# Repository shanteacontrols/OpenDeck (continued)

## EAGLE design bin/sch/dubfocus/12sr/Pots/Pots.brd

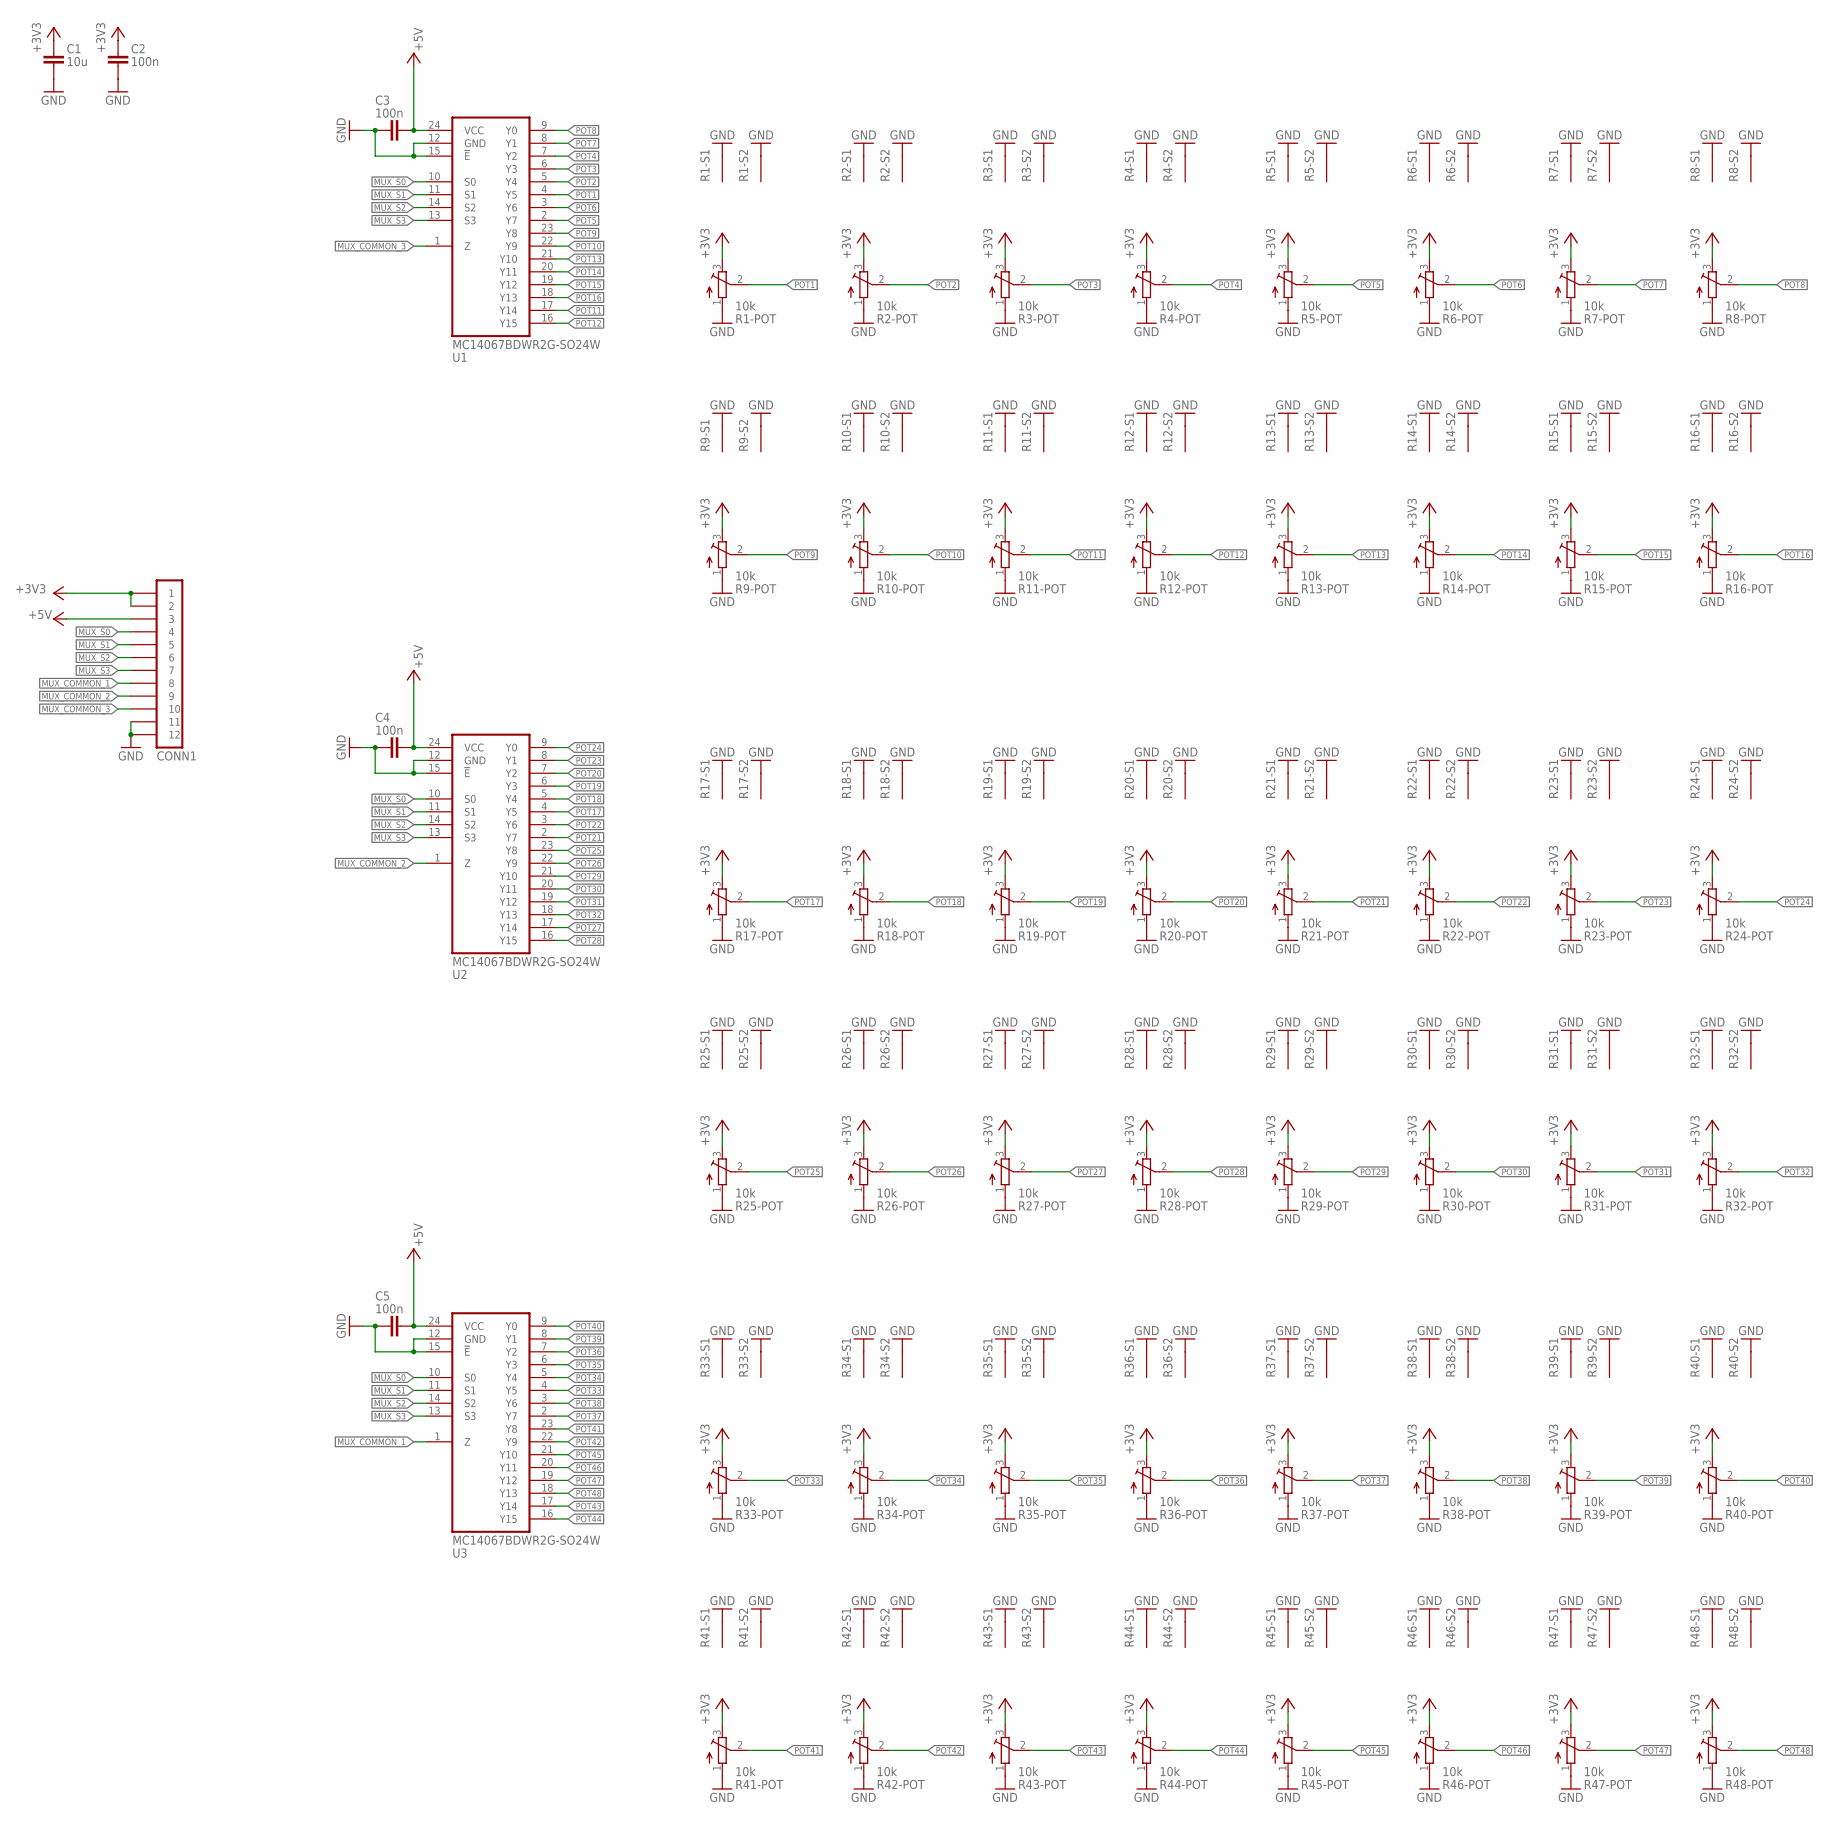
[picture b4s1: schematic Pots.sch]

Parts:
C1: 10u; C0805
C2, C3, C4, C5: 100n; C0805
CONN1: PINHD-1X12-SMD; MOLEX-52271-1279
R1, R2, R3, R4, R5, R6, R7, R8, R9, R10, R11, R12, R13, R14, R15, R16, R17, R18, R19, R20, R21, R22, R23, R24, R25, R26, R27, R28, R29, R30, R31, R32, R33, R34, R35, R36, R37, R38, R39, R40, R41, R42, R43, R44, R45, R46, R47, R48: 10k; PTV09A-4025F-B103
U1, U2, U3: MC14067BDWR2G-SO24W; SO24-W

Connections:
+3V3: C1.1, C2.1, CONN1.1, CONN1.2, R1.3, R2.3, R3.3, R4.3, R5.3, R6.3, R7.3, R8.3, R9.3, R10.3, R11.3, R12.3, R13.3, R14.3, R15.3, R16.3, R17.3, R18.3, R19.3, R20.3, R21.3, R22.3, R23.3, R24.3, R25.3, R26.3, R27.3, R28.3, R29.3, R30.3, R31.3, R32.3, R33.3, R34.3, R35.3, R36.3, R37.3, R38.3, R39.3, R40.3, R41.3, R42.3, R43.3, R44.3, R45.3, R46.3, R47.3, R48.3
+5V: C3.2, C4.2, C5.2, CONN1.3, U1.24 (VCC), U2.24 (VCC), U3.24 (VCC)
GND: C1.2, C2.2, C3.1, C4.1, C5.1, CONN1.11, CONN1.12, R1.1, R1.S1 (S), R1.S2 (S), R2.1, R2.S1 (S), R2.S2 (S), R3.1, R3.S1 (S), R3.S2 (S), R4.1, R4.S1 (S), R4.S2 (S), R5.1, R5.S1 (S), R5.S2 (S), R6.1, R6.S1 (S), R6.S2 (S), R7.1, R7.S1 (S), R7.S2 (S), R8.1, R8.S1 (S), R8.S2 (S), R9.1, R9.S1 (S), R9.S2 (S), R10.1, R10.S1 (S), R10.S2 (S), R11.1, R11.S1 (S), R11.S2 (S), R12.1, R12.S1 (S), R12.S2 (S), R13.1, R13.S1 (S), R13.S2 (S), R14.1, R14.S1 (S), R14.S2 (S), R15.1, R15.S1 (S), R15.S2 (S), R16.1, R16.S1 (S), R16.S2 (S), R17.1, R17.S1 (S), R17.S2 (S), R18.1, R18.S1 (S), R18.S2 (S), R19.1, R19.S1 (S), R19.S2 (S), R20.1, R20.S1 (S), R20.S2 (S), R21.1, R21.S1 (S), R21.S2 (S), R22.1, R22.S1 (S), R22.S2 (S), R23.1, R23.S1 (S), R23.S2 (S), R24.1, R24.S1 (S), R24.S2 (S), R25.1, R25.S1 (S), R25.S2 (S), R26.1, R26.S1 (S), R26.S2 (S), R27.1, R27.S1 (S), R27.S2 (S), R28.1, R28.S1 (S), R28.S2 (S), R29.1, R29.S1 (S), R29.S2 (S), R30.1, R30.S1 (S), R30.S2 (S), R31.1, R31.S1 (S), R31.S2 (S), R32.1, R32.S1 (S), R32.S2 (S), R33.1, R33.S1 (S), R33.S2 (S), R34.1, R34.S1 (S), R34.S2 (S), R35.1, R35.S1 (S), R35.S2 (S), R36.1, R36.S1 (S), R36.S2 (S), R37.1, R37.S1 (S), R37.S2 (S), R38.1, R38.S1 (S), R38.S2 (S), R39.1, R39.S1 (S), R39.S2 (S), R40.1, R40.S1 (S), R40.S2 (S), R41.1, R41.S1 (S), R41.S2 (S), R42.1, R42.S1 (S), R42.S2 (S), R43.1, R43.S1 (S), R43.S2 (S), R44.1, R44.S1 (S), R44.S2 (S), R45.1, R45.S1 (S), R45.S2 (S), R46.1, R46.S1 (S), R46.S2 (S), R47.1, R47.S1 (S), R47.S2 (S), R48.1, R48.S1 (S), R48.S2 (S), U1.12 (GND), U1.15 (!E), U2.12 (GND), U2.15 (!E), U3.12 (GND), U3.15 (!E)
MUX_COMMON_1: CONN1.8, U3.1 (Z)
MUX_COMMON_2: CONN1.9, U2.1 (Z)
MUX_COMMON_3: CONN1.10, U1.1 (Z)
MUX_S0: CONN1.4, U1.10 (S0), U2.10 (S0), U3.10 (S0)
MUX_S1: CONN1.5, U1.11 (S1), U2.11 (S1), U3.11 (S1)
MUX_S2: CONN1.6, U1.14 (S2), U2.14 (S2), U3.14 (S2)
MUX_S3: CONN1.7, U1.13 (S3), U2.13 (S3), U3.13 (S3)
POT1: R1.2, U1.4 (Y5)
POT2: R2.2, U1.5 (Y4)
POT3: R3.2, U1.6 (Y3)
POT4: R4.2, U1.7 (Y2)
POT5: R5.2, U1.2 (Y7)
POT6: R6.2, U1.3 (Y6)
POT7: R7.2, U1.8 (Y1)
POT8: R8.2, U1.9 (Y0)
POT9: R9.2, U1.23 (Y8)
POT10: R10.2, U1.22 (Y9)
POT11: R11.2, U1.17 (Y14)
POT12: R12.2, U1.16 (Y15)
POT13: R13.2, U1.21 (Y10)
POT14: R14.2, U1.20 (Y11)
POT15: R15.2, U1.19 (Y12)
POT16: R16.2, U1.18 (Y13)
POT17: R17.2, U2.4 (Y5)
POT18: R18.2, U2.5 (Y4)
POT19: R19.2, U2.6 (Y3)
POT20: R20.2, U2.7 (Y2)
POT21: R21.2, U2.2 (Y7)
POT22: R22.2, U2.3 (Y6)
POT23: R23.2, U2.8 (Y1)
POT24: R24.2, U2.9 (Y0)
POT25: R25.2, U2.23 (Y8)
POT26: R26.2, U2.22 (Y9)
POT27: R27.2, U2.17 (Y14)
POT28: R28.2, U2.16 (Y15)
POT29: R29.2, U2.21 (Y10)
POT30: R30.2, U2.20 (Y11)
POT31: R31.2, U2.19 (Y12)
POT32: R32.2, U2.18 (Y13)
POT33: R33.2, U3.4 (Y5)
POT34: R34.2, U3.5 (Y4)
POT35: R35.2, U3.6 (Y3)
POT36: R36.2, U3.7 (Y2)
POT37: R37.2, U3.2 (Y7)
POT38: R38.2, U3.3 (Y6)
POT39: R39.2, U3.8 (Y1)
POT40: R40.2, U3.9 (Y0)
POT41: R41.2, U3.23 (Y8)
POT42: R42.2, U3.22 (Y9)
POT43: R43.2, U3.17 (Y14)
POT44: R44.2, U3.16 (Y15)
POT45: R45.2, U3.21 (Y10)
POT46: R46.2, U3.20 (Y11)
POT47: R47.2, U3.19 (Y12)
POT48: R48.2, U3.18 (Y13)

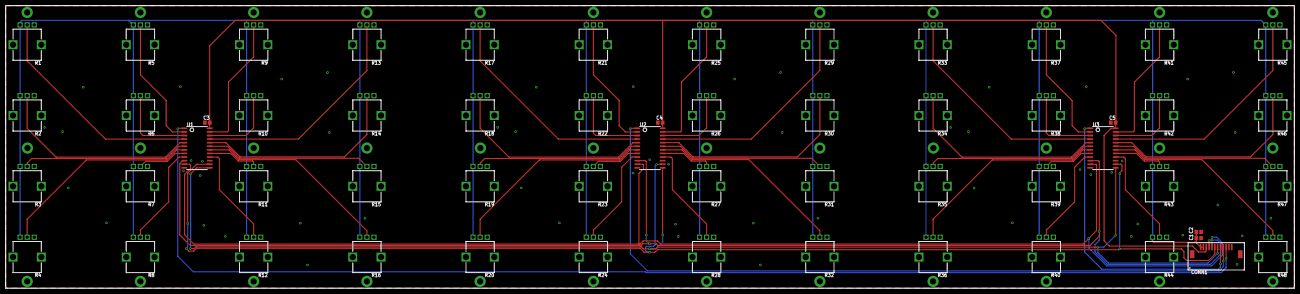
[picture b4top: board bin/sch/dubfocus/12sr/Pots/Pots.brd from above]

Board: 2 copper layers, 455.2 x 99.8 mm, 57 parts (0 on the bottom side), 58 nets.

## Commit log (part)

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2023-05-30 tests/bootloader: don't use internal board api
2023-05-31 clang_tidy_wrapper.sh: use consistent spacing
2023-05-31 vscode: don't hide build dir and compile_commands
2023-05-31 dockerfile: use clang from ubuntu repos
2023-06-01 scripts/dev.sh: always pull the latest image
2023-06-01 dockerfile: fixup comments
2023-06-01 misc: linting
2023-06-04 rewrite the build system in cmake
2023-06-04 tests: guard flash functions with ifdef
2023-06-04 vscode: update devcontainer.json
2023-06-04 update core module
2023-06-04 build/board: rework internal include directories
2023-06-04 board: remove unused function
2023-06-04 tests/hw: make the usage of hw controller configurable in yml config
2023-06-10 build/tests: fix incorrect paths in execute_process
2023-06-10 vscode: fix incorrect path for workspaceFolder
2023-06-10 update sysexconf module
2023-06-10 update midi module
2023-06-10 build/tests: remove redundant include
2023-06-10 build: don't include the entire modules subdir
2023-06-11 build: don't include internal board header in generated target header
2023-06-26 build: move code formatting to script for simpler usage
    otherwise bunch of character escapes are needed in cmake to make it work
2023-06-29 build: fix broken 4051 mux pin generator
2023-06-29 leds: fix invalid retrieval of blink speed
2023-06-29 tests/leds: add tests for single value control types
2023-06-29 system: allow setting 0 as led activation value
2023-09-01 build/scripts: fix muxonmux driver symbol not being generated
2023-10-12 bootloader: remove unsupported code paths
2023-10-14 build: build generated app sources for flashgen target
2023-10-14 touchscreen: don't generate icons from images (unused)
2023-10-15 remove support for viewtech touchscreens
2023-10-16 tests/leds: fix warnings
2023-10-16 build: use named arguments for gen_mcu.sh script
2023-10-26 system: add support for sending din midi clock
2023-10-26 build/gen_mcu.sh: generate only if dir doesn't exist
2023-10-28 sch: place dubfocus 16c schematics in dedicated dir
2024-02-18 build/scripts: allow arbitrary number of daisy chained max7219
2024-02-20 build: always build tests (external project)
2024-02-21 encoders: enable setting lower and upper limit for certain message types
2024-02-21 database: remove unused code
2024-02-21 database: move internal block read/write to dedicated functions
2024-02-21 system: allow disabling of forced refresh after preset change
2024-02-21 display: restore old viewtech display support
2024-03-06 ci: switch to github registry
2024-03-06 scripts/flashing/bmp: use gdb instead of arm-none-eabi-gdb
2024-03-06 ci: update actions
2024-03-06 docker-compose: consistency tweaks
2024-03-06 dockerfile: install nrf command line tools
2024-03-06 build: rework linting script
2024-03-06 vscode: install cortex debug extension
2024-03-06 app: fix include path for logger
2024-03-06 ci: save/restore cache
2024-03-13 display: shorten the MMC record string to fit on display
2024-03-13 display: rework strings and in/out text on display
2024-03-13 display: use U8X8_WITH_USER_PTR symbol for u8x8 lib
2024-03-13 display: show preset number
2024-03-13 display: remove unused variable
2024-03-14 flashgen: namespace the generated mcu header to avoid issues
2024-03-15 system: make preset change with program change in optional
2024-04-02 scripts/flashing: fix pyocd script
2024-04-03 build: regenerate and merge the flash config when application changes
2024-04-06 build: use BUILD_ALWAYS in a consistent way for external projects
    This will ensure that flashgen/sysexgen are rebuilt if they change
2024-04-06 scripts: use sudo in flashing scripts
    This avoids the need for the users to setup udev rules before flashing is possible
2024-04-08 leds: implement static control mode
    In this mode LED is on from the moment the board is powered on or
    since this mode is enabled
2024-04-15 system: set correct upper limit for button value section
2024-04-16 encoders: rename NOTE type to SINGLE_NOTE_VARIABLE_VAL for clarity
2024-04-16 encoders: add the option to send two notes depending on the direction
2024-04-16 encoders: add the option to configure two midi ids
2024-04-16 encoders: tweak the naming of position_t variable
2024-06-12 targets/mega2560_muxsh2: disable touchscreen by default due to high ram usage
2024-11-27 io: use the correct type for digital input states
2024-11-28 ci: update docker workflow
2024-11-28 style: fix formatting
2024-11-28 west: update core module
2024-11-28 devcontainer: add missing privileges
2024-12-02 messaging: add new forcedRefresh flag in event_t
2024-12-02 analog/filter: fix filtering for button message type
2024-12-02 analog/filter: lower the thresholds for digital values
2024-12-02 analog/buttons: make sure analog buttons are forcefully refreshed if requested
2024-12-02 messaging: always init messaging::event_t
2024-12-06 ci: don't edit release body on binaries upload
2024-12-08 style: update linting/formatting
2024-12-09 refactor: system-wide refactoring
    * update to latest libraries
    * rework hwa implementations for hw and tests: implementations are no longer in main.cpp but in module directories instead
    * use common/deps headers for most modules
    * use consistent init order
    * lowercase all the filenames
    * use consistent variable naming
2024-12-09 build: update west projects before the build
2024-12-10 system: rename the class to System (from Instance)
2025-11-14 leds: fix stub class typo
2025-12-17 targets: add support for dubfocus 16t
2025-12-18 buttons: add a new mmc play/stop message type
2025-12-18 misc: remove unused file
2025-12-19 devcontainer: cleanup extensions
2025-12-19 vscode: update settings
2025-12-21 scripts: add jlink flashing script
2025-12-21 vscode: add back the debug configuration and task
2025-12-23 dockerfile: install gdb-multiarch
2025-12-23 leds: rework/fix handling of global midi channel
2025-12-30 scripts: allow running pyocd without probe id
2025-12-31 targets: add indexing to dubfocus16t
2025-12-31 ci: avoid running some workflows on tag
2026-04-01 build: switch to using docker image from zenv repo
2026-04-01 style: update formatting
2026-04-01 style: use static inline where possible
2026-04-08 move sch to root dir
2026-04-09 initial db port
2026-04-09 db port
2026-05-03 refactor: port the entire codebase to zephyr rtos
2026-05-03 refactor: completely revamp emueeprom
2026-05-03 boards: add support for nucleo f767zi
2026-05-03 dts: use common dts definition for usb midi
2026-05-03 build: centralize dts/config parsing
2026-05-03 boards: add support for nucleo f446ze
2026-05-03 refactor: use proper namespacing
2026-05-03 ci: fix ordering
2026-05-03 build: drop some targets from bulk testing/linting
2026-05-03 boards: add support for nrf5340dk
2026-05-07 analog: scan only enabled inputs
2026-05-07 analog: use std::optional for sample reading
2026-05-09 midi: don't send data to usb if not ready
2026-05-12 refactor/feature: implement network/osc capabilities
2026-05-12 refactor: buttons -> switches, leds -> outputs
2026-05-13 network: various improvements
2026-05-14 boards: enable eth on nucleo h7
2026-05-14 style: resolve lint issues
2026-05-14 refactor: isolate mcu specific apis into its own module
2026-05-15 ci: use free space action
2026-05-15 system: simplify skipping of sections in backup
2026-05-15 ci: drop ccache
2026-05-15 refactor: make all includes relative to app/
2026-05-15 misc: formatting
2026-05-16 refactor: isolate hwas into dedicated dirs/libs
2026-05-16 boards: disable usb on nucleo h7/f7
2026-05-16 refactor: isolate builders into dedicated dirs
2026-05-16 analog: fix stub builder
2026-05-18 refactor: make app signaling fully async
    * route signal delivery through the async dispatcher
    * move WebConfig TX/component-info work out of producer callbacks
    * add session IDs so stale WebConfig traffic cannot affect active clients
2026-05-19 refactor: use symbols from app instead of parsing dts in tests
2026-05-19 ci: run lint
2026-05-19 midi: make ble service files part of hwa/hw cmake lib
2026-05-19 refactor: make instances consistently public in test builders
2026-05-19 tests: add missing kconfig options for system test
2026-05-19 tests: add missing module for system test
2026-05-21 usb: increase midi tx queue size
2026-05-21 firmware: increase system workqueue stack size
2026-05-21 boards: add support for wesp32 and olimex esp32 poe boards
2026-05-22 refactor: cleanup bootloader and add mdns
    * use the same construction mechanisms as in firmware
    * use mdns on network targets in bootloader
2026-05-22 dfu: refactor + isolate common parts between app and bootloader
2026-05-23 refactor: use consistent cmake lib names
2026-05-23 refactor: update to latest zlibs + zenv
2026-05-23 refactor: don't import target facts for shared tests
2026-05-23 refactor: reorg/rename tests
2026-05-23 kconfig: move logging kconfig to app dir
2026-05-24 refactor: reorganize shared test headers
2026-05-27 refactor: introduce native pwm support, cleanup pinouts
2026-05-27 refactor: use level based output control
    * drop RGB LED support
    * rename brightness/blink terminology to level/pulse
    * cleanup hwa api for outputs
    * actually implement native row output matrix driver
    * cleanup touchscreen component amount in bindings
2026-05-27 refactor: instantiate mappers directly in io handlers
2026-05-27 misc: cleanup schematics
2026-05-31 refactor: revamp i2c subsystem + implement support for various sensors
2026-06-01 refactor: move hardware linkage into modules
    * move firmware and bootloader hardware library ownership into module CMake files
    * fix WebUSB stub selection for bootloader targets without USB DFU
    * add shared Kconfig.common
2026-06-01 refactor: use opendeck::firmware namespace in fw sources
2026-06-01 refactor: rework module gating depending on target support
    * drop ifdefs around module sources and use cmake guards instead
    * rename some modules for clarity
    * split command handling and event forwarding in websockets into dedicated modules
2026-06-01 refactor: use consistent test files naming
2026-06-01 style: fix lint issues
2026-06-01 tests: misc build fixes
2026-06-01 refactor: add read i2c api
2026-06-02 dts: use random mac address on wiznet boards
2026-06-02 sysbuild: enable target-level network.conf
2026-06-04 refactor: split shared and internal headers
2026-06-04 refactor: flush db writes during config
2026-06-04 boards: tweak partitions on esp3s3
2026-06-04 refactor: implement backpressure on usb dfu, use threaded logging
2026-06-04 i2c: compile sensors only on osc targets
2026-06-04 refactor: qualify missed namespaces
2026-06-04 osc: enable by default
2026-06-04 websockets: drop useless include
2026-06-04 boards: add support for waveshare esp32 s3 eth
2026-06-04 osc: use 4 configured dest ip addresses
2026-06-04 system: add custom req to check if staged dfu is supported
2026-06-04 refactor: drop stale ifdef guards on sources
2026-06-04 boards: add support for wiznet w5500/w6100 eth shields on metro boards
2026-06-05 dts: enable staged update on wiznet pico boards
2026-06-05 fix: use openocd as default runner for f407 discovery
2026-06-05 boards: rename discovery target to discovery_f407g
2026-06-05 mdns: add osc txt metadata
2026-06-06 dts: misc fixes
2026-06-06 build: print each target in newline when calling make with wrong target
2026-06-08 boards: enable uf2 for grand central m4
2026-06-08 i2c: fix scanning on some targets
2026-06-08 dts: tweak partition sizes on esp32
2026-06-08 refactor: add mapper layer for i2c sensors
2026-06-09 database: add missing log line
2026-06-09 dts: tweak partition sizes
2026-06-11 i2c: add support for vl53l5cx sensor
2026-06-11 i2c: remove unused filter
2026-06-11 i2c: normalize the osc sensors paths
2026-06-11 build: drop esp32 targets from bulk lint
2026-06-11 i2c: use minimal filtering on bno085
2026-06-11 refactor: update to latest zlibs
2026-06-11 tests: update system test
2026-06-11 i2c: rework filtering on bno085
2026-06-11 i2c: improve apds9960 responsiveness and add more settings
2026-06-11 add processing osc examples for sensors
2026-06-12 tests/bootloader/dfu: stop depending on generated dfu binary
2026-06-12 ci/docker: optimize and parallelize jobs
2026-06-14 boards: fix support for olimex and wesp32 boards
2026-06-15 update gitattributes
